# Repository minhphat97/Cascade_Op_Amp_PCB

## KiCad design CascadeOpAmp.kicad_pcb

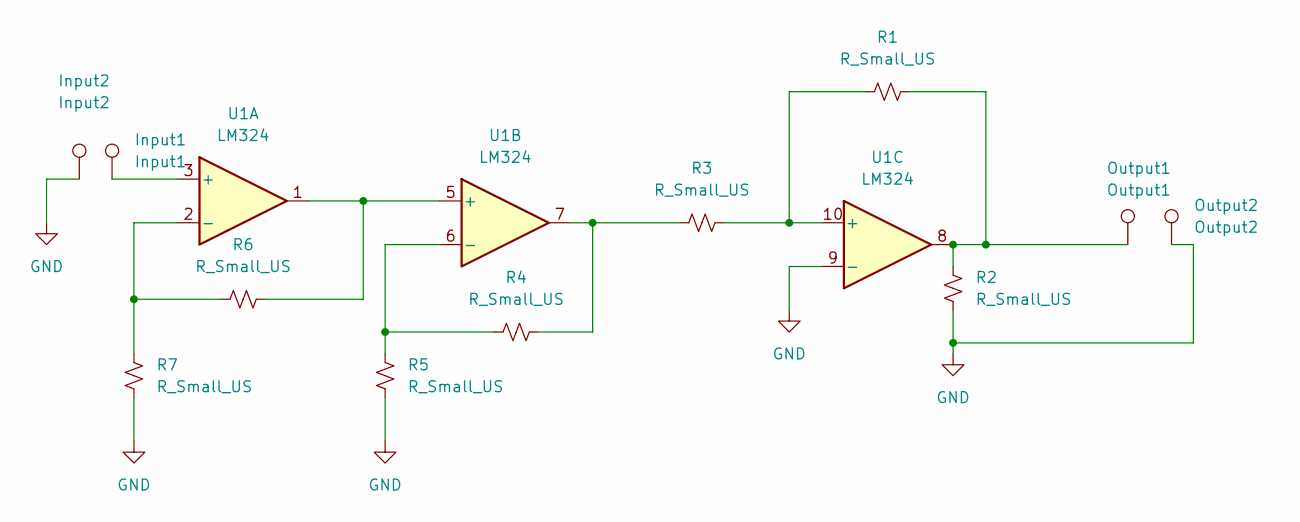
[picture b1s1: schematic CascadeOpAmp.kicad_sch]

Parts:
Input1: Input1; TestPoint_Keystone_5000-5004_Miniature
Input2: Input2; TestPoint_Keystone_5000-5004_Miniature
Output1: Output1; TestPoint_Keystone_5000-5004_Miniature
Output2: Output2; TestPoint_Keystone_5000-5004_Miniature
R1, R2, R3, R4, R5, R6, R7: R_Small_US; R_0603_1608Metric
U1: LM324; DIP-14_W8.89mm_SMDSocket_LongPads

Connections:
GND: Input2.1, Output2.1, R2.1, R5.1, R7.2, U1.9 (-)
unnamed: Output1.1, R1.2, R2.2, U1.8
unnamed: R3.2, R4.1, U1.7
unnamed: Input1.1, U1.3 (+)
unnamed: R6.2, R7.1, U1.2 (-)
unnamed: R6.1, U1.1, U1.5 (+)
unnamed: R4.2, R5.2, U1.6 (-)
unnamed: R1.1, R3.1, U1.10 (+)

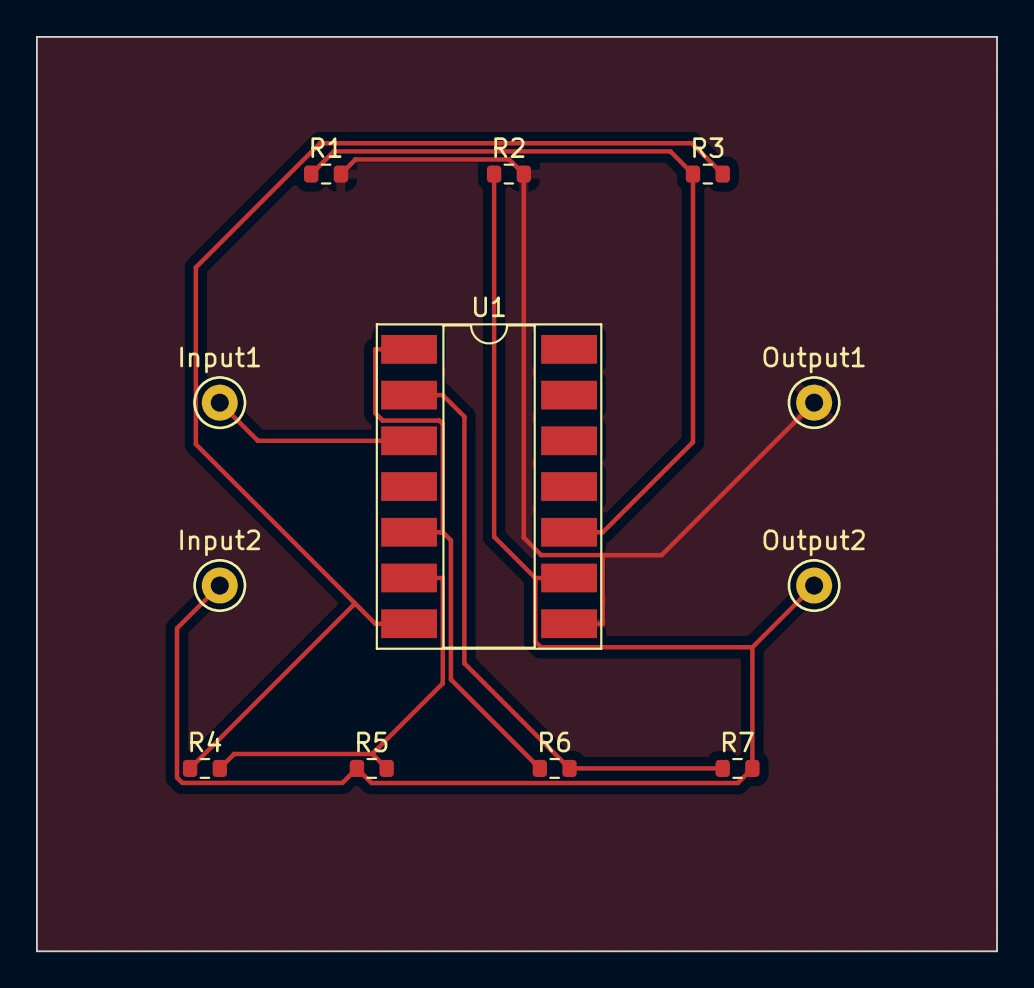
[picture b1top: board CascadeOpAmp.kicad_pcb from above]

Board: 2 copper layers, 53.3 x 50.8 mm, 12 parts (0 on the bottom side), 8 nets.

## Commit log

2023-08-27 Cascade Op Amp PCB
